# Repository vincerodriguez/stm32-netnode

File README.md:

# stm32-netnode

Usb powered stm32f407-based board that reports temperature and telemetry data over ethernet. BME688 is used for the temp sensor, with 1MB flash. SPI and I2C connectors for something in the future, good to have. 
## Status

- [x] Schematic complete
- [x] PCB layout complete  
- [x] v1 boards ordered from JLCPCB (2026-04-19)
- [x] Bring-up
- [x] Firmware MVP
- [x] Deployment

## Specs

| | |
|---|---|
| MCU | STM32F407VET6 (Cortex-M4F @ 168 MHz, 512 KB flash, 192 KB SRAM, 100-LQFP) |
| Ethernet PHY | Microchip LAN8720A, RMII |
| Magjack | Pulse J0011D01BNL |
| Sensor | Bosch BME688 (temperature, humidity, pressure, VOC) |
| Storage | Winbond W25Q80DVUXIE SPI NOR, 8 MBIT (1MB) |
| Power | USB-C, 5 V → 3.3 V via AP2112K-3.3 LDO |
| PCB | 60 × 60 mm, 4-layer, JLCPCB |
| Firmware | C - LWIP, ST-HAL (planned port to Rust) |

## Repo layout
hardware/ KiCad project structure
docs/ Design documentation and ADRs
firmware/ C firmware / Rust (coming soon)
test/ Bring-up checklists and general bring-up headaches

## Documents

- [Requirements](docs/01-design.md) *(coming)*
- [Architecture](docs/02-architecture.md) 
- [Decision records](docs/03-bringup-analysis.md) *(coming)*

## License

MIT

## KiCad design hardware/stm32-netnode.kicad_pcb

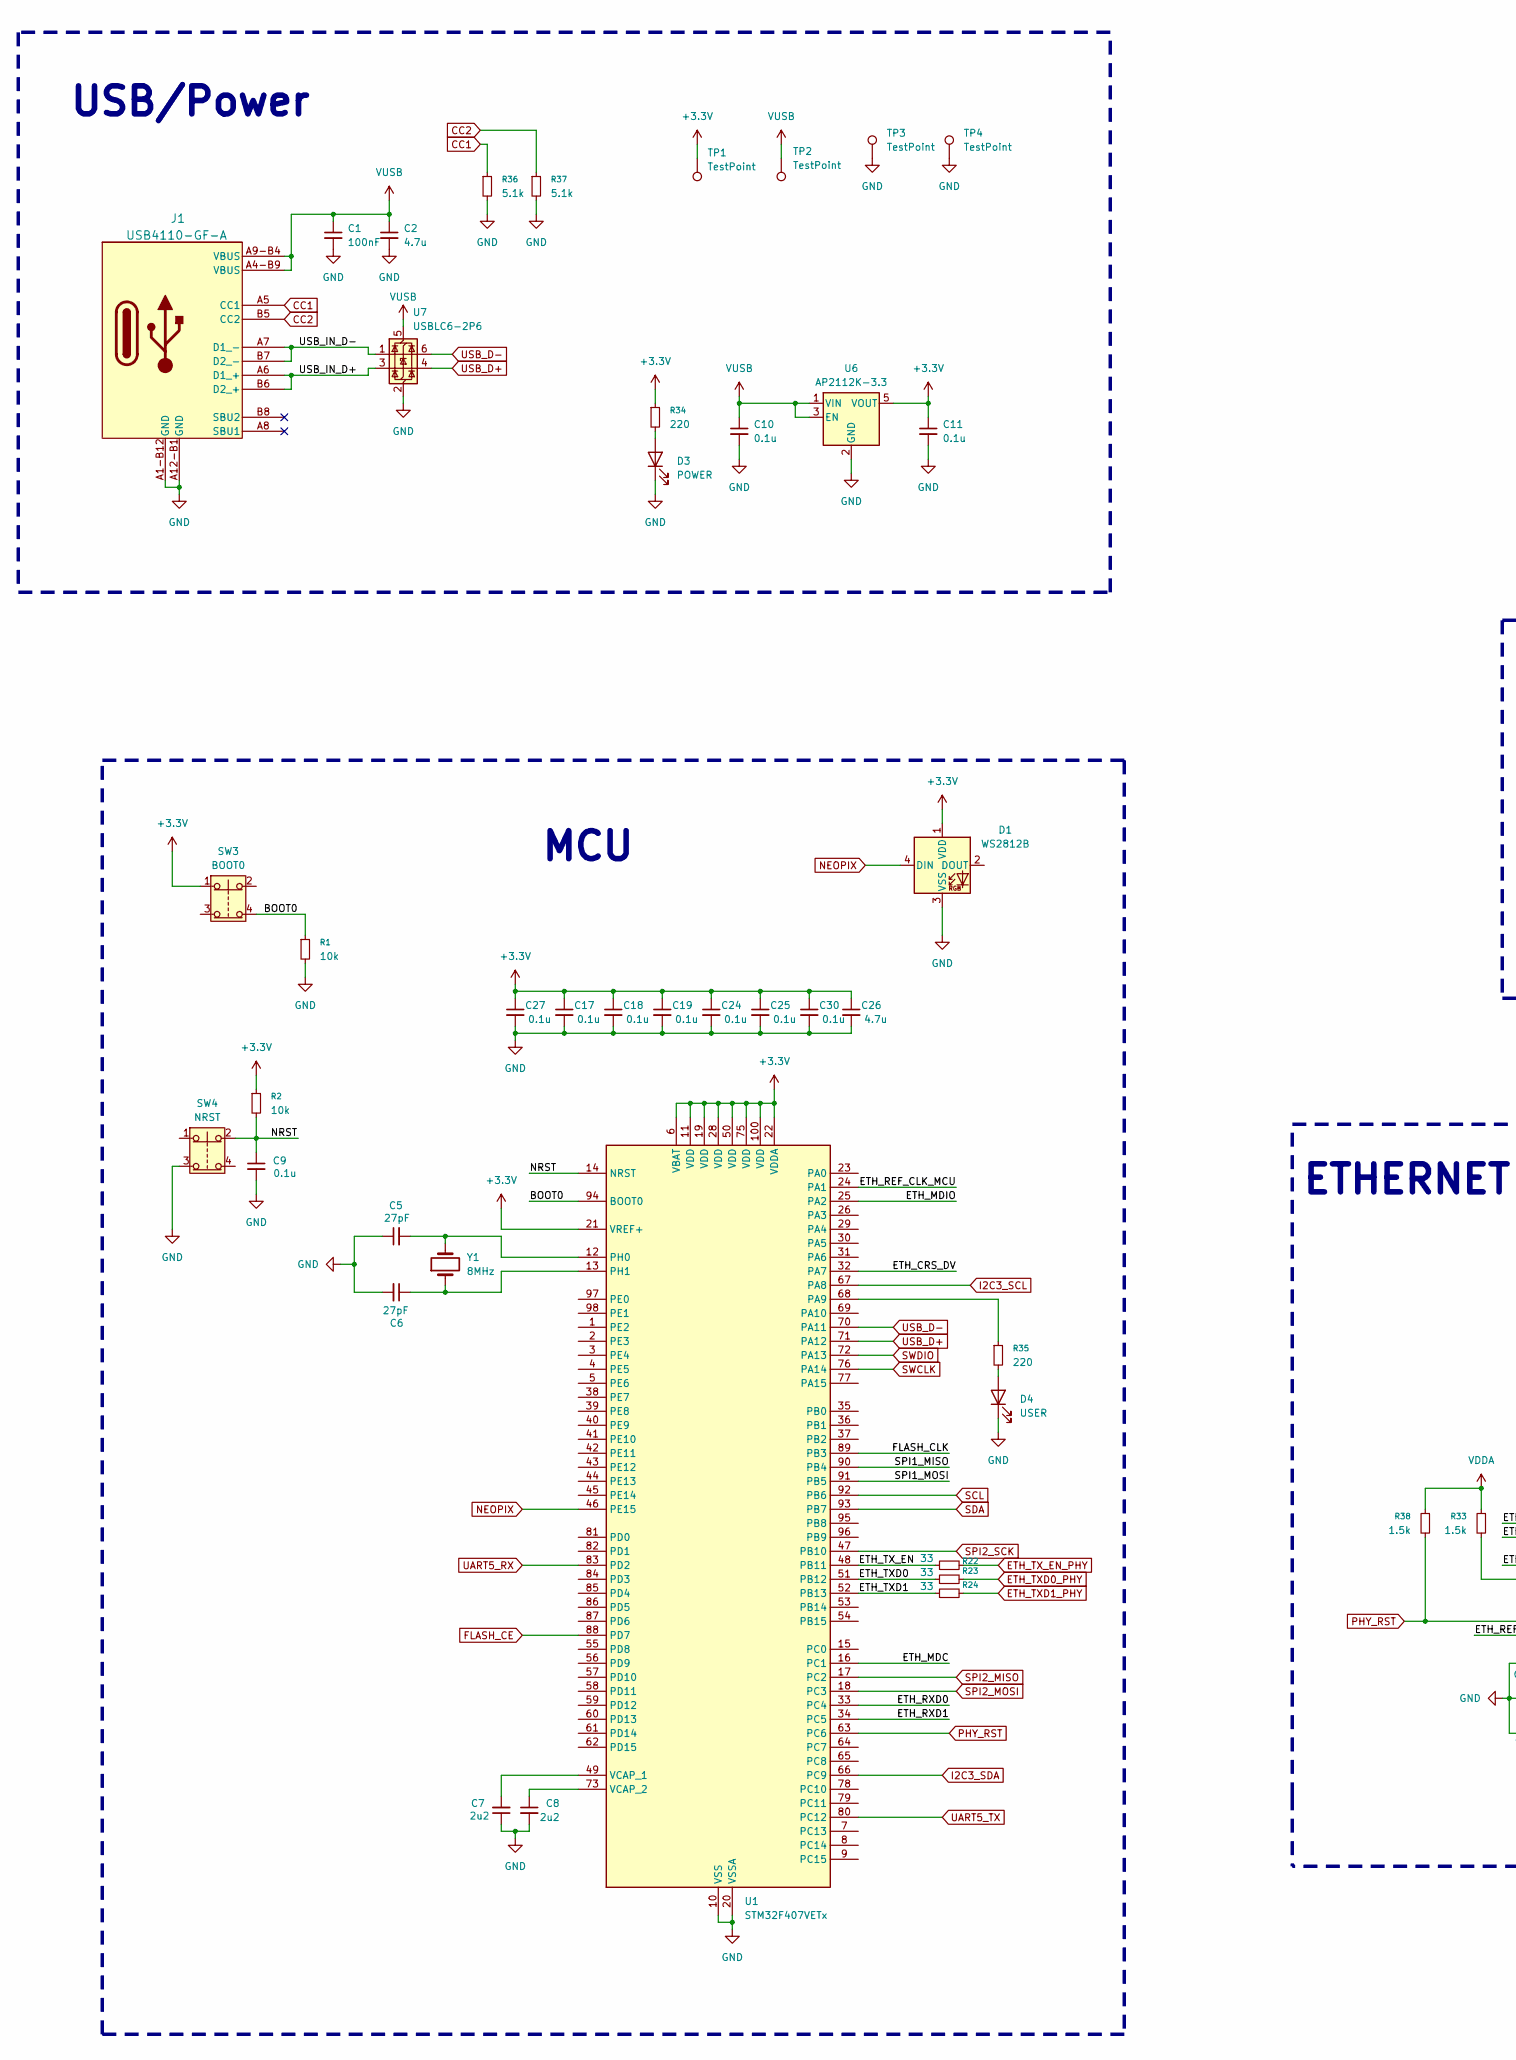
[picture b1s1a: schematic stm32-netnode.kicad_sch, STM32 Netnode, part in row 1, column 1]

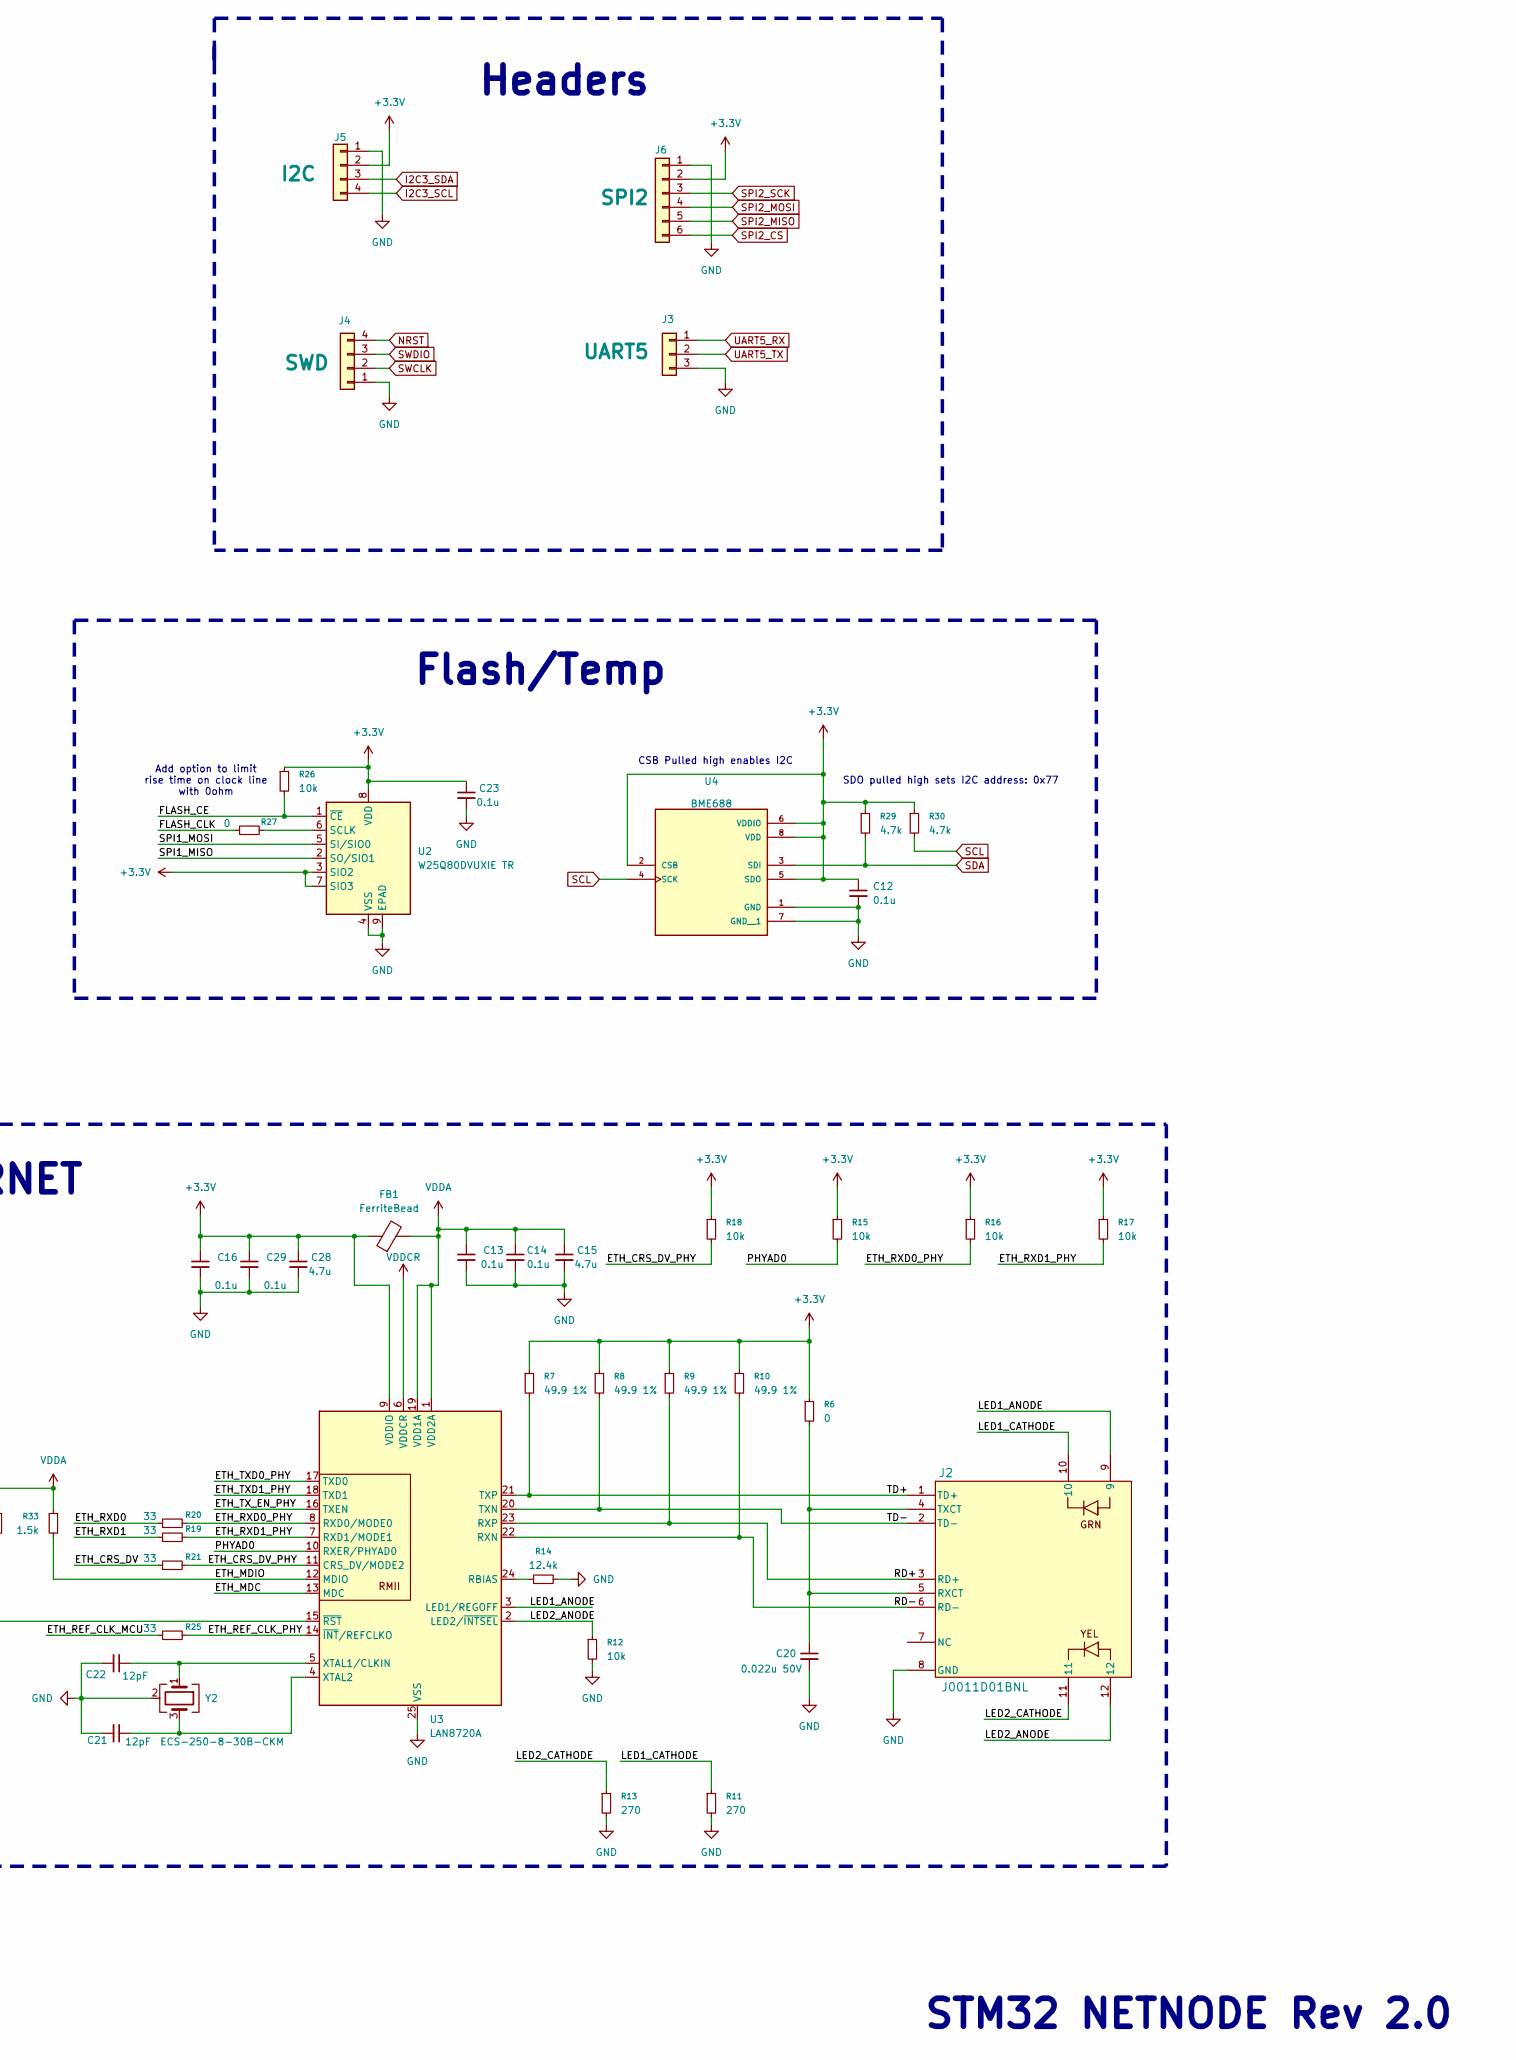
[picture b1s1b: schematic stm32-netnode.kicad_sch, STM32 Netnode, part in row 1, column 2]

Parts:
C1: 100nF; C_0603_1608Metric
C2: 4.7u; C_0603_1608Metric
C5, C6: 27pF; C_0603_1608Metric
C7, C8: 2u2; C_0603_1608Metric
C9, C10, C11, C12, C13, C14, C16, C17, C18, C19, C23, C24, C25, C27, C29, C30: 0.1u; C_0603_1608Metric
C15, C26, C28: 4.7u; C_0805_2012Metric
C20: 0.022u 50V; C_0603_1608Metric
C21, C22: 12pF; C_0402_1005Metric
D1: WS2812B; LED_WS2812B_PLCC4_5.0x5.0mm_P3.2mm
D3: POWER; LED_0603_1608Metric
D4: USER; LED_0603_1608Metric
FB1: FerriteBead; L_0603_1608Metric
J1: USB4110-GF-A; USB4110-GF-A_GCT
J2: J0011D01BNL; CONN12_011D01BNL_PUL
J3: UART5; PinHeader_1x03_P2.54mm_Vertical
J4: SWD; PinHeader_1x04_P2.54mm_Vertical
J5: I2C; CONN4_BM04B-SRSS_JST
J6: SPI2; CONN_BM06B-SRSS-TB_JST
R1, R2, R12, R15, R16, R17, R18, R26: 10k; R_0603_1608Metric
R6, R27: 0; R_0603_1608Metric
R7, R8, R9, R10: 49.9 1%; R_0603_1608Metric
R11, R13: 270; R_0603_1608Metric
R14: 12.4k; R_0603_1608Metric
R19, R20, R21, R22, R23, R24, R25: 33; R_0603_1608Metric
R29, R30: 4.7k; R_0603_1608Metric
R33, R38: 1.5k; R_0603_1608Metric
R34, R35: 220; R_0603_1608Metric
R36, R37: 5.1k; R_0603_1608Metric
SW3: BOOT0; SW_7914J-1-000E
SW4: NRST; SW_7914J-1-000E
TP1, TP2, TP3, TP4: TestPoint; TestPoint_Pad_D1.5mm
U1: STM32F407VETx; LQFP-100_14x14mm_P0.5mm
U2: W25Q80DVUXIE TR; Winbond_USON-8-1EP_3x2mm_P0.5mm_EP0.2x1.6mm
U3: LAN8720A; VQFN-24-1EP_4x4mm_P0.5mm_EP2.5x2.5mm_ThermalVias
U4: BME688; IC_BME688; PARTREV 1.0
U6: AP2112K-3.3; SOT-23-5
U7: USBLC6-2P6; SOT-666
Y1: 8MHz; Crystal_SMD_HC49-SD
Y2: ECS-250-8-30B-CKM; XTAL_ECS-250-8-30B-CKM

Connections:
+3.3V: C11.1, C12.1, C16.1, C17.1, C18.1, C19.1, C23.1, C24.1, C25.1, C26.1, C27.1, C28.1, C29.1, C30.1, D1.1 (VDD), FB1.1, J5.2, J6.2, R2.1, R6.1, R7.1, R8.1, R9.1, R10.1, R15.1, R16.1, R17.1, R18.1, R26.1, R29.1, R30.1, R34.1, SW3.1, TP1.1 (1_1), U1.6 (VBAT), U1.11 (VDD), U1.19 (VDD), U1.21 (VREF+), U1.22 (VDDA), U1.28 (VDD), U1.50 (VDD), U1.75 (VDD), U1.100 (VDD), U2.3 (SIO2), U2.7 (SIO3), U2.8 (VDD), U3.9 (VDDIO), U4.2 (CSB), U4.5 (SDO), U4.6 (VDDIO), U4.8 (VDD), U6.5 (VOUT)
/BOOT0: R1.1, SW3.4, U1.94 (BOOT0)
/ETH_CRS_DV: R21.1, U1.32 (PA7)
/ETH_CRS_DV_PHY: R18.2, R21.2, U3.11 (CRS_DV/MODE2)
/ETH_MDC: U1.16 (PC1), U3.13 (MDC)
/ETH_MDIO: R33.2, U1.25 (PA2), U3.12 (MDIO)
/ETH_REF_CLK_MCU: R25.1, U1.24 (PA1)
/ETH_REF_CLK_PHY: R25.2, U3.14 (~INT/REFCLKO)
/ETH_RXD0: R20.1, U1.33 (PC4)
/ETH_RXD0_PHY: R16.2, R20.2, U3.8 (RXD0/MODE0)
/ETH_RXD1: R19.1, U1.34 (PC5)
/ETH_RXD1_PHY: R17.2, R19.2, U3.7 (RXD1/MODE1)
/ETH_TXD0: R23.1, U1.51 (PB12)
/ETH_TXD1: R24.1, U1.52 (PB13)
/ETH_TX_EN: R22.1, U1.48 (PB11)
/FLASH_CLK: R27.1, U1.89 (PB3)
/LED1_ANODE: J2.9, U3.3 (LED1/REGOFF)
/LED1_CATHODE: J2.10, R11.1
/LED2_ANODE: J2.12, R12.1, U3.2 (LED2/~INTSEL)
/LED2_CATHODE: J2.11, R13.1
/PHYAD0: R15.2, U3.10 (RXER/PHYAD0)
/RD+: J2.3 (RD+), R9.2, U3.23 (RXP)
/RD-: J2.6 (RD-), R10.2, U3.22 (RXN)
/SPI1_MISO: U1.90 (PB4), U2.2 (SO/SIO1)
/SPI1_MOSI: U1.91 (PB5), U2.5 (SI/SIO0)
/TD+: J2.1 (TD+), R7.2, U3.21 (TXP)
/TD-: J2.2 (TD-), R8.2, U3.20 (TXN)
/USB_IN_D+: J1.A6 (D1_+), J1.B6 (D2_+), U7.3 (I/O2)
/USB_IN_D-: J1.A7 (D1_-), J1.B7 (D2_-), U7.1 (I/O1)
CC1: J1.A5 (CC1), R36.1
CC2: J1.B5 (CC2), R37.1
ETH_TXD0_PHY: R23.2, U3.17 (TXD0)
ETH_TXD1_PHY: R24.2, U3.18 (TXD1)
ETH_TX_EN_PHY: R22.2, U3.16 (TXEN)
FLASH_CE: R26.2, U1.88 (PD7), U2.1 (~CE)
GND: C1.2, C2.2, C5.1, C6.2, C7.1, C8.2, C9.2, C10.2, C11.2, C12.2, C13.2, C14.2, C15.2, C16.2, C17.2, C18.2, C19.2, C20.2, C21.2, C22.2, C23.2, C24.2, C25.2, C26.2, C27.2, C28.2, C29.2, C30.2, D1.3 (VSS), D3.1 (K), D4.1 (K), J1.A1-B12 (GND), J1.A12-B1 (GND), J2.8 (GND), J3.3, J4.1, J5.1, J6.1, R1.2, R11.2, R12.2, R13.2, R14.2, R36.2, R37.2, SW4.3, TP3.1 (1_1), TP4.1 (1_1), U1.10 (VSS), U1.20 (VSSA), U1.27 (VSS), U1.74 (VSS), U1.99 (VSS), U2.4 (VSS), U2.9 (EPAD), U3.25 (VSS), U4.1 (GND), U4.7 (GND__1), U6.2 (GND), U7.2 (GND), Y2.2 (G), Y2.4 (G)
I2C3_SCL: J5.4, U1.67 (PA8)
I2C3_SDA: J5.3, U1.66 (PC9)
NEOPIX: D1.4 (DIN), U1.46 (PE15)
NRST: C9.1, J4.4, R2.2, SW4.2, U1.14 (NRST)
unnamed: D3.2 (A), R34.2
unnamed: D4.2 (A), R35.2
unnamed: C20.1, J2.4 (TXCT), J2.5 (RXCT), R6.2
unnamed: R35.1, U1.68 (PA9)
unnamed: C5.2, U1.12 (PH0), Y1.2
unnamed: C6.1, U1.13 (PH1), Y1.1
unnamed: C7.2, U1.49 (VCAP_1)
unnamed: C8.1, U1.73 (VCAP_2)
unnamed: R27.2, U2.6 (SCLK)
unnamed: R14.1, U3.24 (RBIAS)
unnamed: C22.1, U3.5 (XTAL1/CLKIN), Y2.1
unnamed: C21.1, U3.4 (XTAL2), Y2.3
PHY_RST: R38.2, U1.63 (PC6), U3.15 (~RST)
SCL: R30.2, U1.92 (PB6), U4.4 (SCK)
SDA: R29.2, U1.93 (PB7), U4.3 (SDI)
SPI2_CS: J6.6
SPI2_MISO: J6.5, U1.17 (PC2)
SPI2_MOSI: J6.4, U1.18 (PC3)
SPI2_SCK: J6.3, U1.47 (PB10)
SWCLK: J4.2, U1.76 (PA14)
SWDIO: J4.3, U1.72 (PA13)
UART5_RX: J3.1, U1.83 (PD2)
UART5_TX: J3.2, U1.80 (PC12)
USB_D+: U1.71 (PA12), U7.4 (I/O2)
USB_D-: U1.70 (PA11), U7.6 (I/O1)
VDDA: C13.1, C14.1, C15.1, FB1.2, R33.1, R38.1, U3.1 (VDD2A), U3.19 (VDD1A)
VDDCR: U3.6 (VDDCR)
VUSB: C1.1, C2.1, C10.1, J1.A4-B9 (VBUS), J1.A9-B4 (VBUS), TP2.1 (1_1), U6.1 (VIN), U6.3 (EN), U7.5 (VBUS)

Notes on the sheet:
ETHERNET
CSB Pulled high enables I2C
Flash/Temp
SDO pulled high sets I2C address: 0x77
USB/Power
STM32 NETNODE Rev 2.0
Add option to limit rise time on clock line with 0ohm
Headers
MCU

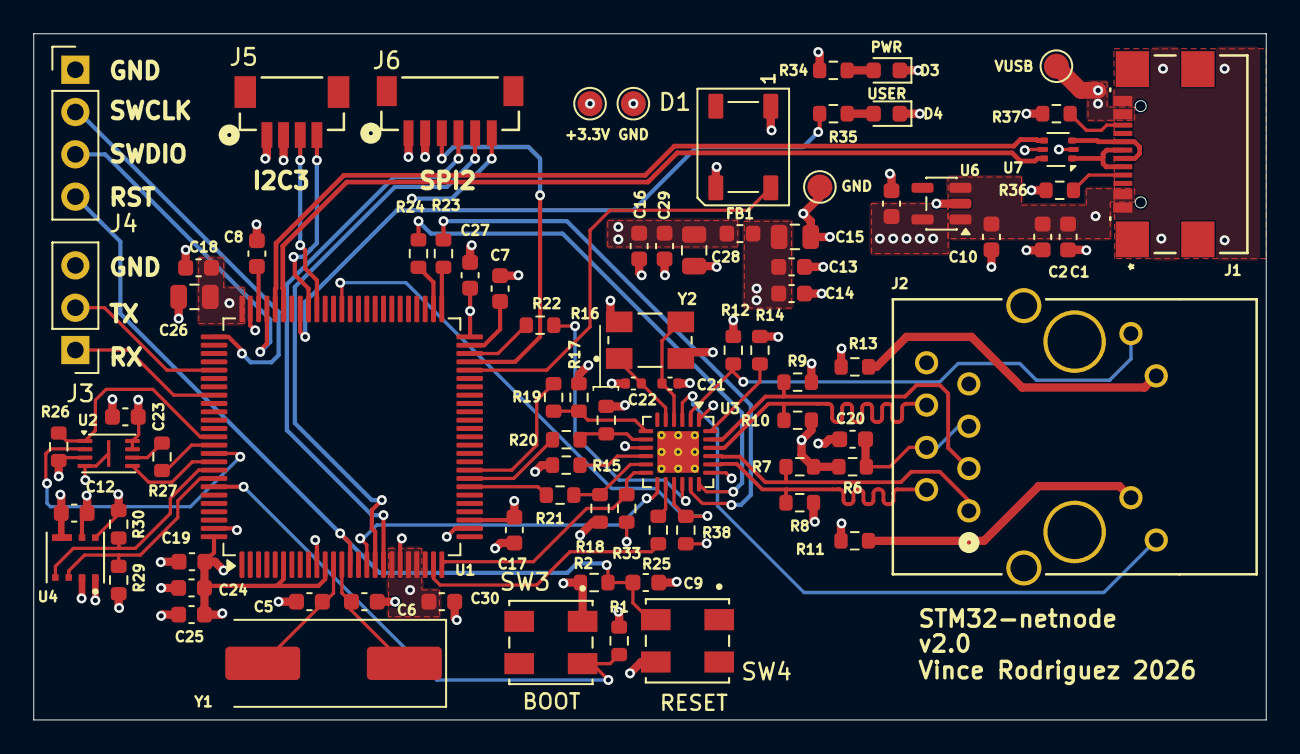
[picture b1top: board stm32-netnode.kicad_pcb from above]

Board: 4 copper layers, 74.0 x 41.2 mm, 84 parts (0 on the bottom side), 66 nets.

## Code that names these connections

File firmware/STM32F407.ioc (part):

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Mcu.Name=STM32F407V(E-G)Tx
Mcu.Package=LQFP100
Mcu.UserName=STM32F407VETx
PA1.Mode=RMII
PA1.Signal=ETH_REF_CLK
PA13.Mode=Serial_Wire
PA13.Signal=SYS_JTMS-SWDIO
PA14.Mode=Serial_Wire
PA14.Signal=SYS_JTCK-SWCLK
PA2.Mode=RMII
PA2.Signal=ETH_MDIO
PA7.Mode=RMII
PA7.Signal=ETH_CRS_DV
PA9.GPIOParameters=GPIO_Label
PA9.GPIO_Label=LED
PA9.Signal=GPIO_Output
PB0.GPIOParameters=GPIO_Label
PB0.GPIO_Label=FLASH_CE
PB0.Signal=GPIO_Output
PB11.Mode=RMII
PB11.Signal=ETH_TX_EN
PB12.Mode=RMII
PB12.Signal=ETH_TXD0
PB13.Mode=RMII
PB13.Signal=ETH_TXD1
PB3.Mode=Full_Duplex_Master
PB3.Signal=SPI1_SCK
PB4.Mode=Full_Duplex_Master
PB4.Signal=SPI1_MISO
PB5.Mode=Full_Duplex_Master
PB5.Signal=SPI1_MOSI
PB6.Mode=I2C
PB6.Signal=I2C1_SCL
PB7.Mode=I2C
PB7.Signal=I2C1_SDA
PC1.Mode=RMII
PC1.Signal=ETH_MDC
PC12.Mode=Asynchronous
PC12.Signal=UART5_TX
PC4.Mode=RMII
PC4.Signal=ETH_RXD0
PC5.Mode=RMII
PC5.Signal=ETH_RXD1
PC6.GPIOParameters=GPIO_Label
PC6.GPIO_Label=PHY_RST
PC6.Signal=GPIO_Output
PD2.Mode=Asynchronous
PD2.Signal=UART5_RX
PH0-OSC_IN.Mode=HSE-External-Oscillator
PH0-OSC_IN.Signal=RCC_OSC_IN
PH1-OSC_OUT.Mode=HSE-External-Oscillator
PH1-OSC_OUT.Signal=RCC_OSC_OUT
RCC.HSE_VALUE=8000000
RCC.SYSCLKFreq_VALUE=168000000
RCC.SYSCLKSource=RCC_SYSCLKSOURCE_PLLCLK
board=custom

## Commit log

2026-04-19 Initial commit scheamtic and layout for version 1.0
2026-04-19 add first readme
2026-04-19 add documentation skeleton
2026-05-06 Radd rev 2.0
2026-05-06 schematic rev 2.0
2026-05-11 Add firmware and documentation
